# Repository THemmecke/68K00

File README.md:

# 68K00
68000 Board EAGLE/VHDL
This repository contains EAGLE and VHDL sources for a 68000 based SBC. The ECB based SBC provides a 68000 cpu, 24 bit address and 16bit databus, 1 or 2 MB SRAM and up to 512KB FLASH on board, 12(C)887 RTC. It can be used with the GDP-FPGA (https://github.com/THemmecke/GDPFPGAII) to constitute a complete microcomputer system.

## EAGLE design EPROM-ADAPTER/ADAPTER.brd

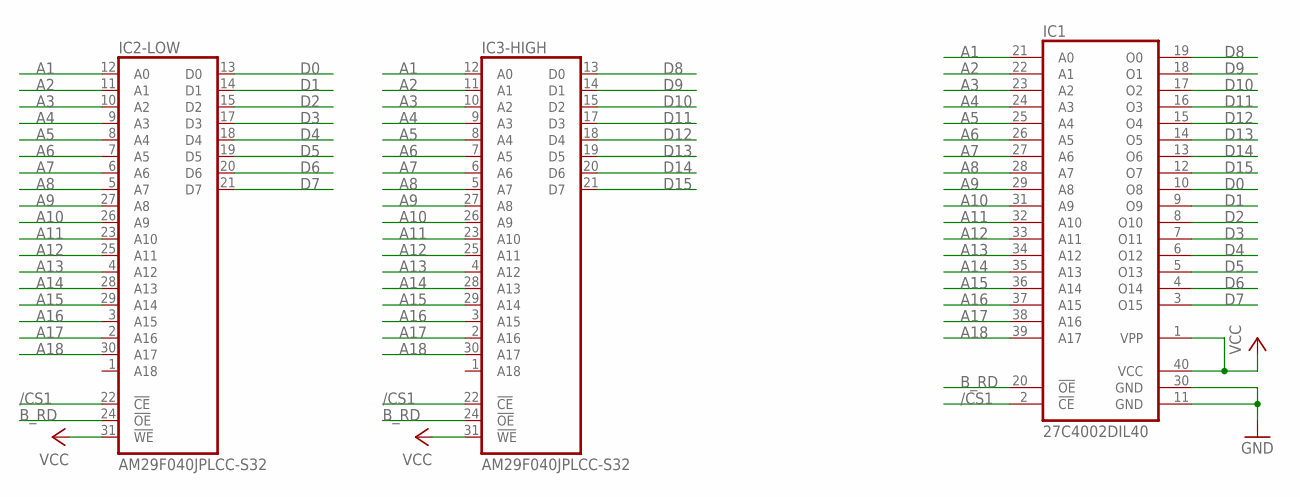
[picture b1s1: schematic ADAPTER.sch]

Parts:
IC1: 27C4002DIL40; DIL40
IC2-LOW, IC3-HIGH: AM29F040JPLCC-S32; PLCC-S32

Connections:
/CS1: IC1.2 (!CE), IC2-LOW.22 (!CE), IC3-HIGH.22 (!CE)
A1: IC1.21 (A0), IC2-LOW.12 (A0), IC3-HIGH.12 (A0)
A2: IC1.22 (A1), IC2-LOW.11 (A1), IC3-HIGH.11 (A1)
A3: IC1.23 (A2), IC2-LOW.10 (A2), IC3-HIGH.10 (A2)
A4: IC1.24 (A3), IC2-LOW.9 (A3), IC3-HIGH.9 (A3)
A5: IC1.25 (A4), IC2-LOW.8 (A4), IC3-HIGH.8 (A4)
A6: IC1.26 (A5), IC2-LOW.7 (A5), IC3-HIGH.7 (A5)
A7: IC1.27 (A6), IC2-LOW.6 (A6), IC3-HIGH.6 (A6)
A8: IC1.28 (A7), IC2-LOW.5 (A7), IC3-HIGH.5 (A7)
A9: IC1.29 (A8), IC2-LOW.27 (A8), IC3-HIGH.27 (A8)
A10: IC1.31 (A9), IC2-LOW.26 (A9), IC3-HIGH.26 (A9)
A11: IC1.32 (A10), IC2-LOW.23 (A10), IC3-HIGH.23 (A10)
A12: IC1.33 (A11), IC2-LOW.25 (A11), IC3-HIGH.25 (A11)
A13: IC1.34 (A12), IC2-LOW.4 (A12), IC3-HIGH.4 (A12)
A14: IC1.35 (A13), IC2-LOW.28 (A13), IC3-HIGH.28 (A13)
A15: IC1.36 (A14), IC2-LOW.29 (A14), IC3-HIGH.29 (A14)
A16: IC1.37 (A15), IC2-LOW.3 (A15), IC3-HIGH.3 (A15)
A17: IC1.38 (A16), IC2-LOW.2 (A16), IC3-HIGH.2 (A16)
A18: IC1.39 (A17), IC2-LOW.30 (A17), IC3-HIGH.30 (A17)
B_RD: IC1.20 (!OE), IC2-LOW.24 (!OE), IC3-HIGH.24 (!OE)
D0: IC1.10 (O8), IC2-LOW.13 (D0)
D1: IC1.9 (O9), IC2-LOW.14 (D1)
D2: IC1.8 (O10), IC2-LOW.15 (D2)
D3: IC1.7 (O11), IC2-LOW.17 (D3)
D4: IC1.6 (O12), IC2-LOW.18 (D4)
D5: IC1.5 (O13), IC2-LOW.19 (D5)
D6: IC1.4 (O14), IC2-LOW.20 (D6)
D7: IC1.3 (O15), IC2-LOW.21 (D7)
D8: IC1.19 (O0), IC3-HIGH.13 (D0)
D9: IC1.18 (O1), IC3-HIGH.14 (D1)
D10: IC1.17 (O2), IC3-HIGH.15 (D2)
D11: IC1.16 (O3), IC3-HIGH.17 (D3)
D12: IC1.15 (O4), IC3-HIGH.18 (D4)
D13: IC1.14 (O5), IC3-HIGH.19 (D5)
D14: IC1.13 (O6), IC3-HIGH.20 (D6)
D15: IC1.12 (O7), IC3-HIGH.21 (D7)
GND: IC1.11 (GND), IC1.30 (GND), IC2-LOW.16 (GND), IC3-HIGH.16 (GND)
VCC: IC1.1 (VPP), IC1.40 (VCC), IC2-LOW.31 (!WE), IC2-LOW.32 (VCC), IC3-HIGH.31 (!WE), IC3-HIGH.32 (VCC)

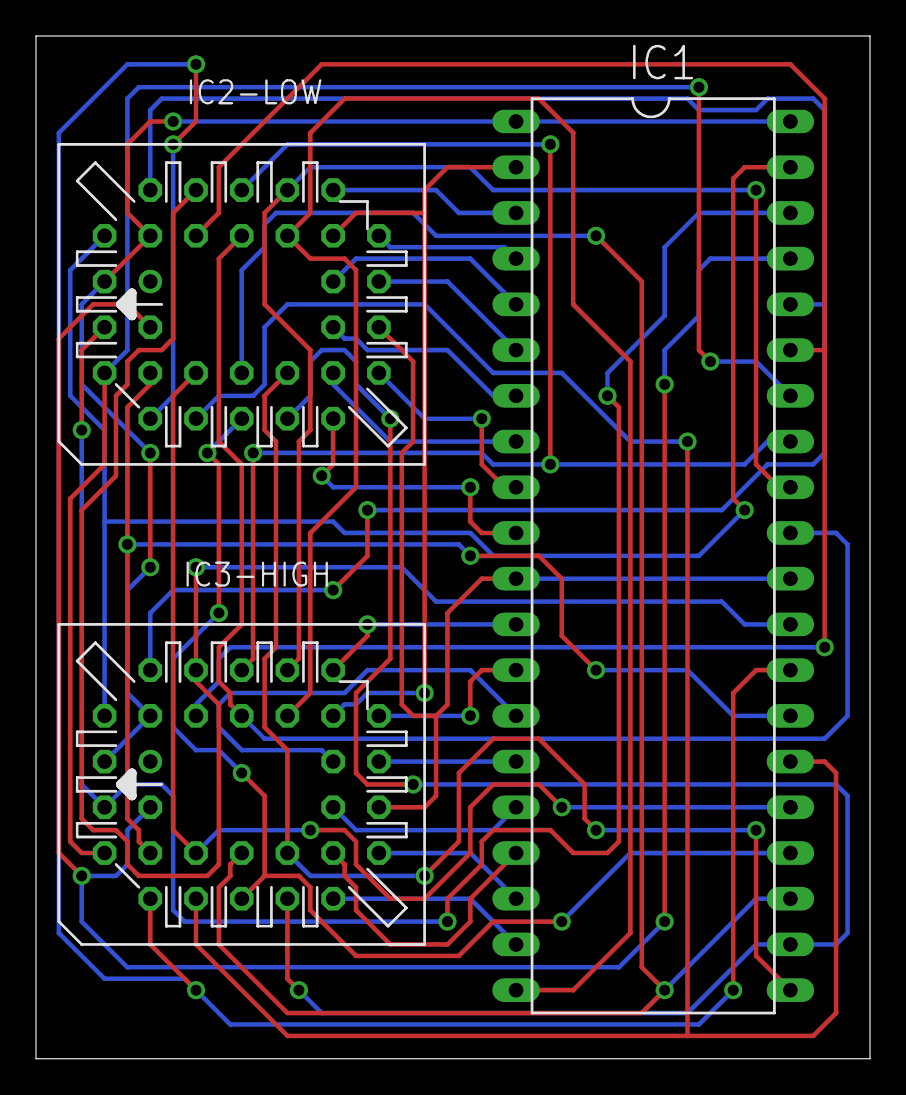
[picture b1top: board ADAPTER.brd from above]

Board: 2 copper layers, 46.3 x 56.8 mm, 3 parts (0 on the bottom side), 38 nets.

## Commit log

2015-11-06 Update Author
2016-06-10 no message
